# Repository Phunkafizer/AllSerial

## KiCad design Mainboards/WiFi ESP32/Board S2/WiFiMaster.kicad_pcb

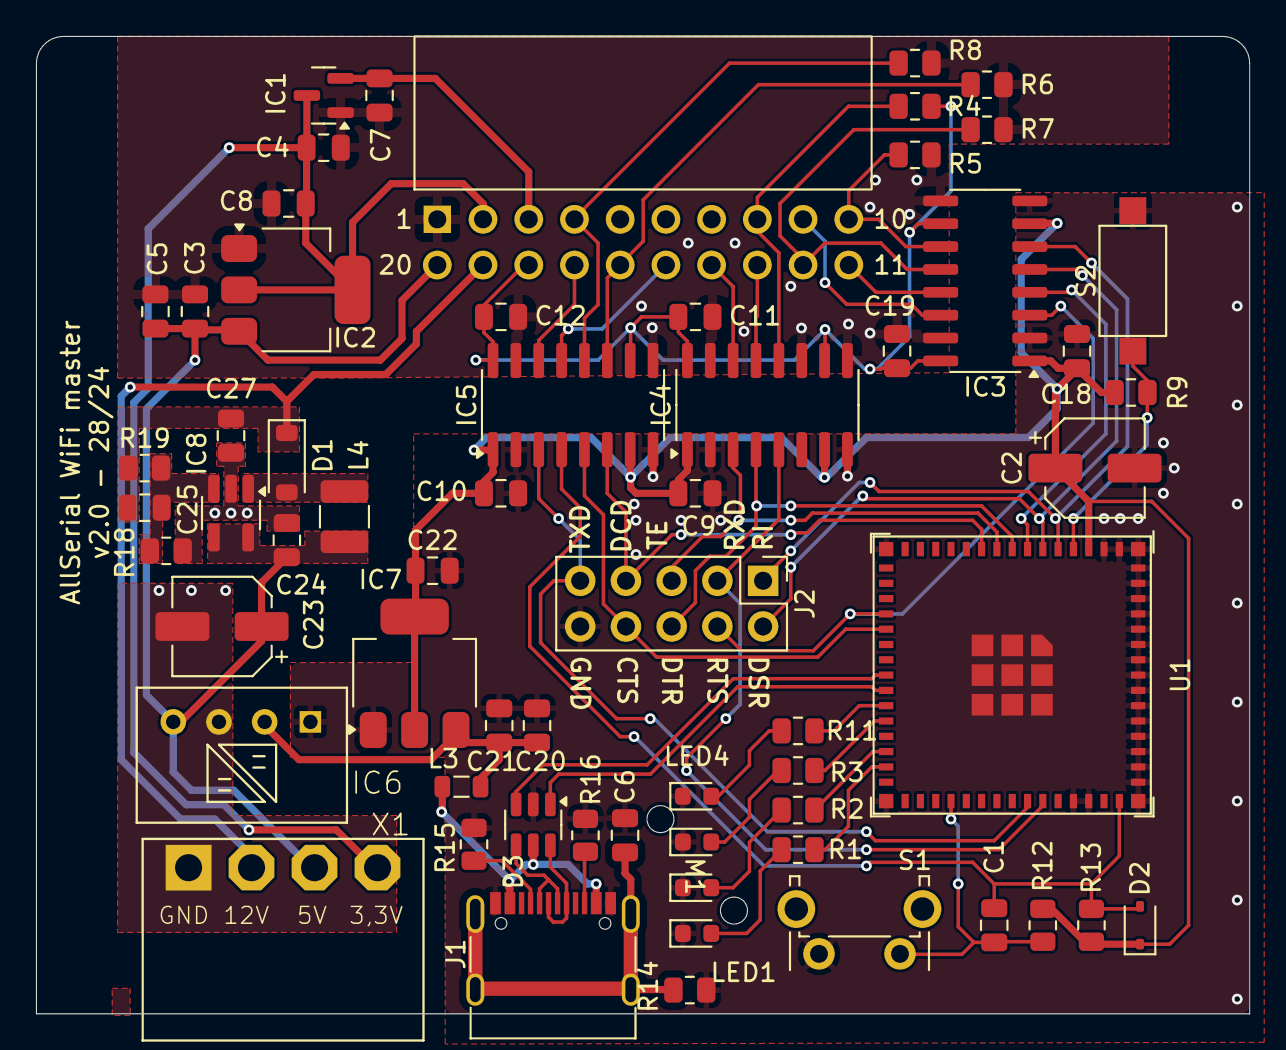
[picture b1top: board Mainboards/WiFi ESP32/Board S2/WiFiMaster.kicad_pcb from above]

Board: 2 copper layers, 67.4 x 54.3 mm, 63 parts (0 on the bottom side), 51 nets.

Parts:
C1, C5, C8, C21, C22, C27: 10µ; C_0805_2012Metric
C2, C23: 100µ; CP_Elec_5x5.9
C3, C9, C10, C11, C12, C18, C19, C20: 100n; C_0805_2012Metric
C4, C7: 1µ; C_0805_2012Metric
C6: 10n; C_0805_2012Metric
C24: 4µ7; C_0805_2012Metric
C25: 22pF; C_0805_2012Metric
D1: MBR0530; D_SOD-123
D2: 1N4148WS; D_SOD-323
D3: USBLC6-2; SOT-23-6
IC1: MCP170X; SOT-23
IC2, IC7: NCP1117ST; SOT-223-3_TabPin2
IC3, IC4, IC5: ADuM142E1BRZ; SOIC-16_3.9x9.9mm_P1.27mm
IC6: IL0505; XPPOWER-ILxxxxS
IC8: TPS61041; SOT-23-5_HandSoldering
J1: USB_C_Receptacle_USB2.0; USB_C_Receptacle_G-Switch_GT-USB-7010ASV
J2: Conn_02x05_Odd_Even; PinHeader_2x05_P2.54mm_Vertical
L3: WE-CBF_0805; L_0805_2012Metric
L4: 10µ; L_1210_3225Metric
LED1: red; LED_0603_1608Metric
LED2: green; LED_0603_1608Metric
LED3: yellow; LED_0603_1608Metric
LED4: blue; LED_0603_1608Metric
M1: Mentor 1296.1004
R1, R2, R3: 120; R_0805_2012Metric
R4, R5, R6, R7, R8: 10k; R_0805_2012Metric
R9, R13, R18: 33k; R_0805_2012Metric
R11: 22; R_0805_2012Metric
R12: 3k3; R_0805_2012Metric
R14: 1M; R_0805_2012Metric
R15, R16: 5k1; R_0805_2012Metric
R19: 300k; R_0805_2012Metric
S1: 31-XX; SW_Tactile_SPST_Angled_PTS645Vx58-2LFS
S2: SW_SPST_CK_RS282G05A3
U1: ESP32-S3-MINI-1; ESP32-S3-MINI-1U
X1: AKL18X-04W; AKL182-04
X2: ALLSERIALMASTERM; MasterBoard

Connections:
+1V8: C7.1, IC1.2 (VO), X2.3 (+1.8V)
+3.3V: C2.1, C9.1, C10.1, C18.1, C22.1, D2.1 (K), IC3.1 (VDDA), IC3.7 (ENA), IC4.1 (VDDA), IC4.7 (ENA), IC5.1 (VDDA), IC5.7 (ENA), IC7.2 (VO), R9.2, R12.2, R13.2, U1.3 (3V3)
+3V3_2: C4.1, C8.1, IC1.3 (VI), IC2.2 (VO), X1.P$4 (S), X2.2 (+3.3V)
+5V: C20.1, C21.1, IC6.2 (+VIN), IC7.3 (VI), L3.2
+5V_2: C3.1, C5.1, C23.1, C24.1, IC2.3 (VI), IC6.4 (+VOUT), IC8.4 (EN), IC8.5 (VIN), L4.1, X1.P$3 (S), X2.20 (+5V)
+12V: C25.1, C27.1, D1.1 (K), R19.1, X1.P$2 (S), X2.19 (+12V)
/BTN: C1.2, R12.1, S1.1, U1.34 (GPIO38)
/CTS_A: IC5.5 (OUTA), J2.8, U1.20 (GPIO16)
/CTS_B: IC5.12 (INB), R8.1, X2.4 (CTS)
/DCD_A: IC5.6 (OUTA), J2.7, U1.10 (GPIO6)
/DCD_B: IC5.11 (INB), R6.1, X2.16 (DCD)
/DSR_A: IC3.5 (OUTA), J2.2, U1.6 (GPIO2)
/DSR_B: IC3.12 (INB), R7.1, X2.12 (DSR)
/DTR_A: IC4.4 (INA), J2.6, U1.8 (GPIO4)
/DTR_B: IC4.13 (OUTB), X2.13 (DTR)
/GP_A: IC3.4 (INA), U1.7 (GPIO3)
/GP_B: IC3.13 (OUTB), X2.11 (GPIO)
/LED1: R1.2, U1.29 (GPIO34)
/LED2: R2.1, U1.28 (GPIO33)
/LED3: R3.1, U1.26 (GPIO26)
/LED4: R11.1, U1.25 (GPIO21)
/RI_A: IC3.6 (OUTA), J2.1, U1.5 (GPIO1)
/RI_B: IC3.11 (INB), R5.1, X2.10 (RI)
/RST: C1.1, D2.2 (A), IC5.4 (INA), R13.1, U1.45 (EN)
/RST_B: IC5.13 (OUTB), X2.15 (RST)
/RTS_A: IC3.3 (INA), J2.4, U1.19 (GPIO15)
/RTS_B: IC3.14 (OUTB), X2.9 (RTS)
/RXD_A: IC4.5 (OUTA), J2.3, U1.40 (GPIO44)
/RXD_B: IC4.12 (INB), R4.2, X2.8 (RXD)
/SHLD: C6.1, J1.S1 (SHIELD), R14.2
/TXD_A: IC5.3 (INA), J2.9, U1.39 (GPIO43)
/TXD_B: IC5.14 (OUTB), X2.17 (TXD)
/TXEN_A: IC4.3 (INA), J2.5, U1.9 (GPIO5)
/TXEN_B: IC4.14 (OUTB), X2.14 (TXEN)
/USB_D+: D3.1 (I/O1), U1.24 (GPIO20)
/USB_D-: D3.3 (I/O2), U1.23 (GPIO19)
GND: C2.2, C6.2, C9.2, C10.2, C18.2, C20.2, C21.2, C22.2, D3.2 (GND), IC3.2 (GNDA), IC3.8 (GNDA), IC4.2 (GNDA), IC4.8 (GNDA), IC5.2 (GNDA), IC5.8 (GNDA), IC6.1 (-VIN), IC7.1 (GND), J1.A1 (GND), J1.A12 (GND), J1.B1 (GND), J1.B12 (GND), J2.10, LED1.1 (K), LED2.1 (K), LED3.1 (K), LED4.1 (K), R14.1, R15.2, R16.2, S1.2, S2.2, U1.1 (GND), U1.2 (GND), U1.42 (GND), U1.43 (GND), U1.46 (GND), U1.47 (GND), U1.48 (GND), U1.49 (GND), U1.50 (GND), U1.51 (GND), U1.52 (GND), U1.53 (GND), U1.54 (GND), U1.55 (GND), U1.56 (GND), U1.57 (GND), U1.58 (GND), U1.59 (GND), U1.60 (GND), U1.61 (GND), U1.62 (GND), U1.63 (GND), U1.64 (GND), U1.65 (GND)
GND2: C3.2, C4.2, C5.2, C7.2, C8.2, C11.2, C12.2, C19.2, C23.2, C24.2, C27.2, IC1.1 (GND), IC2.1 (GND), IC3.9 (GNDB), IC3.15 (GNDB), IC4.9 (GNDB), IC4.11 (INB), IC4.15 (GNDB), IC5.9 (GNDB), IC5.15 (GNDB), IC6.3 (-VOUT), IC8.2 (GND), R5.2, R6.2, R7.2, R8.2, R18.2, X1.P$1 (S), X2.1 (GND)
unnamed: D1.2 (A), IC8.1 (SW), L4.2
unnamed: D3.6 (I/O1), J1.A6 (D+), J1.B6 (D+)
unnamed: D3.4 (I/O2), J1.A7 (D-), J1.B7 (D-)
unnamed: D3.5 (VBUS), J1.A4 (VBUS), J1.A9 (VBUS), J1.B4 (VBUS), J1.B9 (VBUS), L3.1
unnamed: C25.2, IC8.3 (FB), R18.1, R19.2
unnamed: J1.A5 (CC1), R15.1
unnamed: J1.B5 (CC2), R16.1
unnamed: LED1.2 (A), R1.1
unnamed: LED2.2 (A), R2.2
unnamed: LED3.2 (A), R3.2
unnamed: LED4.2 (A), R11.2
unnamed: R9.1, S2.1, U1.4 (GPIO0)
VBUS: C11.1, C12.1, C19.1, IC3.10 (ENB), IC3.16 (VDDB), IC4.10 (ENB), IC4.16 (VDDB), IC5.10 (ENB), IC5.16 (VDDB), R4.1, X2.18 (VIN)

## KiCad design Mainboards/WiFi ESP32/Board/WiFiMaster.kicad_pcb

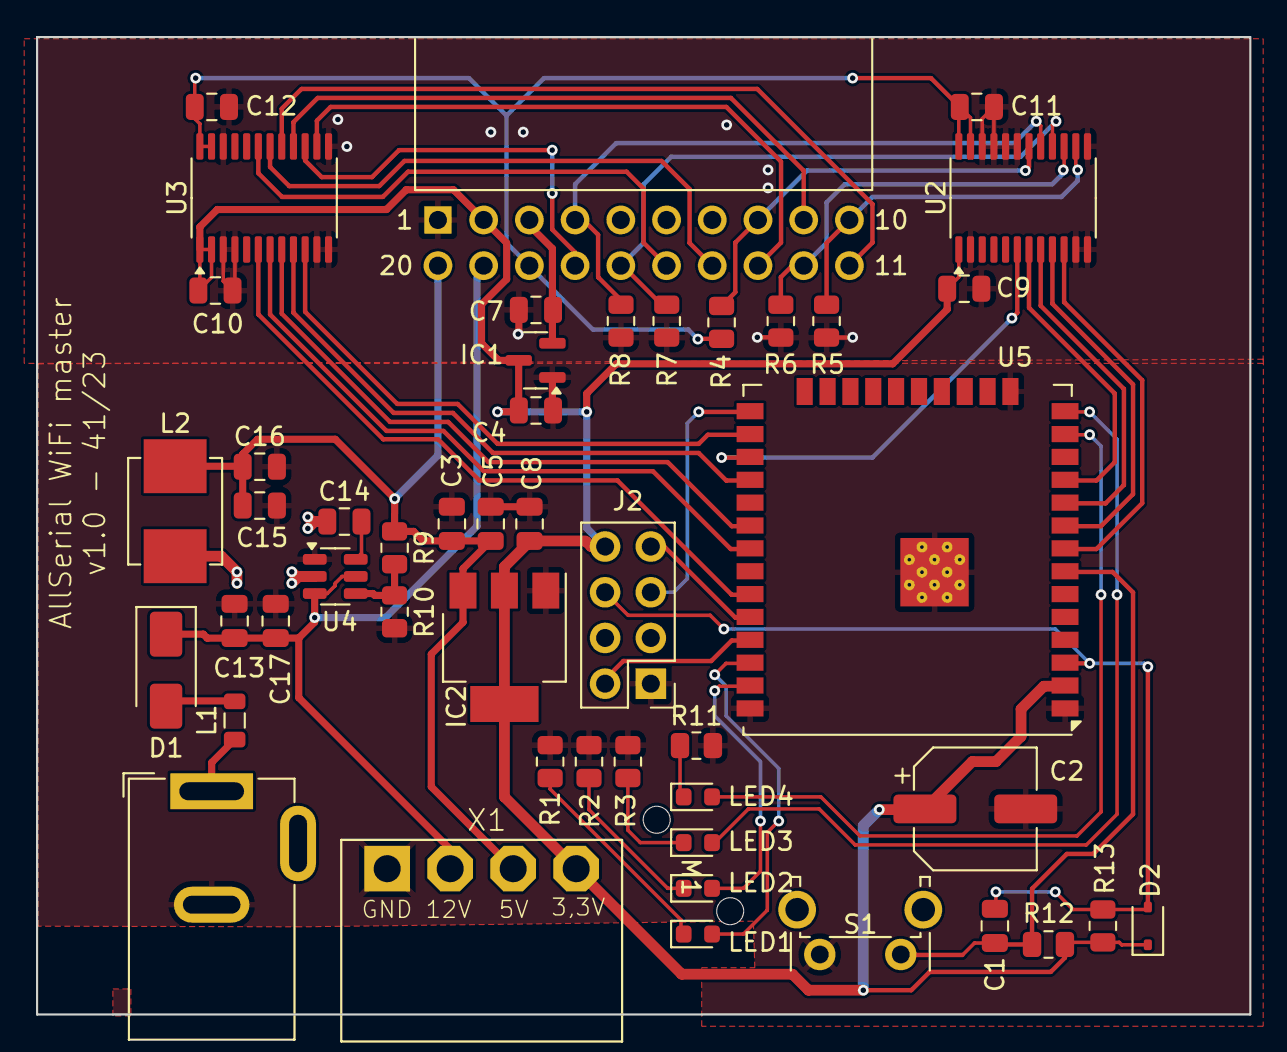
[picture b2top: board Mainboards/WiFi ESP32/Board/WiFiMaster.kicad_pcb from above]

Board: 2 copper layers, 67.4 x 54.3 mm, 49 parts (0 on the bottom side), 45 nets.

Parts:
C1, C5, C8, C13, C17: 10µ; C_0805_2012Metric
C2: 100µ; CP_Elec_6.3x5.4
C3, C9, C10, C11, C12, C14: 100n; C_0805_2012Metric
C4, C7: 1µ; C_0805_2012Metric
C15, C16: 22µ; C_0805_2012Metric
D1: SK 14 DIO; D_SMA
D2: 1N4148WS; D_SOD-323
IC1: MCP170X; SOT-23
IC2: NCP1117ST; SOT-223-3_TabPin2
J1: Barrel_Jack_Switch; BarrelJack_GCT_DCJ200-10-A_Horizontal
J2: Conn_02x04_Odd_Even; PinHeader_2x04_P2.54mm_Vertical
L1: WE-CBF_0805; L_0805_2012Metric
L2: 4µ7; L_Murata_LQH55DN_5.7x5.0mm
LED1: red; LED_0603_1608Metric
LED2: green; LED_0603_1608Metric
LED3: yellow; LED_0603_1608Metric
LED4: blue; LED_0603_1608Metric
M1: Mentor 1296.1004
R1, R2, R3: 120; R_0805_2012Metric
R4, R5, R6, R7, R8, R10: 10k; R_0805_2012Metric
R9: 54k9; R_0805_2012Metric
R11: 22; R_0805_2012Metric
R12: 3k3; R_0805_2012Metric
R13: 33k; R_0805_2012Metric
S1: 31-XX; SW_Tactile_SPST_Angled_PTS645Vx58-2LFS
U2, U3: SN74LVC8T245; TSSOP-24_4.4x7.8mm_P0.65mm
U4: TPS56220; SOT-23-6
U5: ESP32-WROOM-32U
X1: AKL18X-04W; AKL182-04
X2: ALLSERIALMASTERM; MasterBoard

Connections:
+1V8: C7.1, IC1.2 (VO), X2.3 (+1.8V)
+3.3V: C2.1, C4.1, C8.1, C9.1, C10.1, D2.1 (K), IC1.3 (VI), IC2.2 (VO), J2.8, R12.2, R13.2, U2.1 (Vcca), U3.1 (Vcca), U3.2 (DIR), U5.2 (VDD), X1.P$4 (S), X2.2 (+3.3V)
+5V: C3.1, C5.1, C15.1, C16.1, IC2.3 (VI), L2.2, R9.1, X1.P$3 (S), X2.20 (+5V)
+12V: C13.1, C17.1, D1.1 (K), U4.3 (VIN), U4.5 (EN), X1.P$2 (S), X2.19 (+12V)
/BTN: C1.2, R12.1, S1.1, U5.7 (IO35)
/CTS_A: U2.7 (A5), U5.11 (IO26)
/CTS_B: R8.1, U2.17 (B5), X2.4 (CTS)
/DCD_A: U2.8 (A6), U5.10 (IO25)
/DCD_B: R7.1, U2.16 (B6), X2.16 (DCD)
/DSR_A: U2.9 (A7), U5.9 (IO33)
/DSR_B: R6.1, U2.15 (B7), X2.12 (DSR)
/DTR_A: U3.10 (A8), U5.26 (IO4)
/DTR_B: U3.14 (B8), X2.13 (DTR)
/GP_A: U3.7 (A5), U5.31 (IO19)
/GP_B: U3.17 (B5), X2.11 (GPIO)
/IO0: J2.5, U5.25 (IO0)
/LED1: LED1.2 (A), U5.36 (IO22)
/LED2: LED2.2 (A), U5.37 (IO23)
/LED3: LED3.2 (A), U5.14 (IO12)
/LED4: LED4.2 (A), U5.13 (IO14)
/RI_A: U2.10 (A8), U5.8 (IO32)
/RI_B: R5.1, U2.14 (B8), X2.10 (RI)
/RST: C1.1, D2.2 (A), J2.6, R13.1, U5.3 (EN)
/RST_B: U3.19 (B3), X2.15 (RST)
/RTS_A: U3.8 (A6), U5.30 (IO18)
/RTS_B: U3.16 (B6), X2.9 (RTS)
/RXD: J2.7, U5.34 (RXD0/IO3)
/RXD_A: U2.6 (A4), U5.27 (IO16)
/RXD_B: R4.2, U2.18 (B4), X2.8 (RXD)
/TXD: J2.2, U5.35 (TXD0/IO1)
/TXD_A: U3.9 (A7), U5.28 (IO17)
/TXD_B: U3.15 (B7), X2.17 (TXD)
/TXEN_A: U3.6 (A4), U5.33 (IO21)
/TXEN_B: U3.18 (B4), X2.14 (TXEN)
GND: C2.2, C3.2, C4.2, C5.2, C7.2, C8.2, C9.2, C10.2, C11.2, C12.2, C13.2, C15.2, C16.2, C17.2, IC1.1 (GND), IC2.1 (GND), J1.2, J2.1, R1.1, R2.2, R3.2, R5.2, R6.2, R7.2, R8.2, R10.2, R11.2, S1.2, U2.2 (DIR), U2.11 (GND), U2.12 (GND), U2.13 (GND), U2.19 (B3), U2.20 (B2), U2.21 (B1), U2.22 (OE), U3.3 (A1), U3.4 (A2), U3.11 (GND), U3.12 (GND), U3.13 (GND), U3.22 (OE), U4.1 (GND), U5.1 (GND), U5.15 (GND), U5.38 (GND), U5.39 (GND), X1.P$1 (S), X2.1 (GND)
unnamed: D1.2 (A), L1.2
unnamed: J1.1, L1.1
unnamed: LED1.1 (K), R1.2
unnamed: LED2.1 (K), R2.1
unnamed: LED3.1 (K), R3.1
unnamed: LED4.1 (K), R11.1
unnamed: C14.2, U4.6 (BOOT)
unnamed: R9.2, R10.1, U4.4 (FB)
unnamed: C14.1, L2.1, U4.2 (SW)
VBUS: C11.1, C12.1, R4.1, U2.23 (Vccb), U2.24 (Vccb), U3.23 (Vccb), U3.24 (Vccb), X2.18 (VIN)

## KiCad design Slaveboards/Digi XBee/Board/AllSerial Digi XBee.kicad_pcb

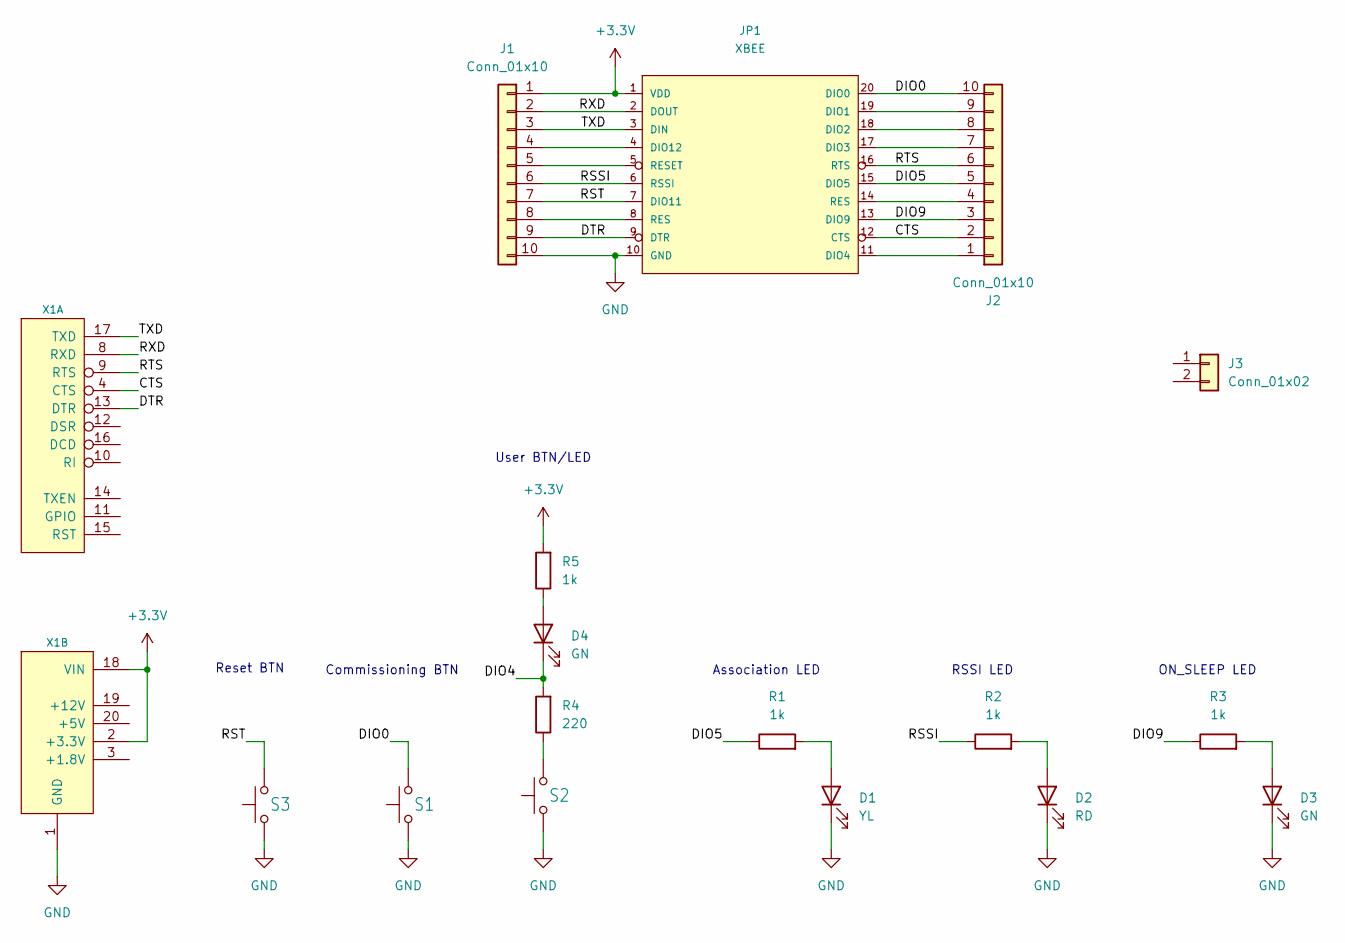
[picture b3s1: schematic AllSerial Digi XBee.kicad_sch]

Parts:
D1: YL; LED_0805_2012Metric
D2: RD; LED_0805_2012Metric
D3, D4: GN; LED_0805_2012Metric
J1, J2: Conn_01x10; PinHeader_1x10_P2.54mm_Vertical
J3: Conn_01x02; Metz_PT11302HBBN_182
JP1: XBEE
R1, R2, R3, R5: 1k; R_0805_2012Metric
R4: 220; R_0805_2012Metric
S1, S2, S3: 31-XX; SW_SPST_CK_RS282G05A3; LCSC C2837543
X1: AllSerial Slaveboard; SlaveBoard

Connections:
+3.3V: J1.1, JP1.1 (VDD), R5.2, X1.2 (+3.3V), X1.18 (VIN)
/CTS: J2.2, JP1.12 (CTS), X1.4 (CTS)
/DIO0: J2.10, JP1.20 (DIO0), S1.1
/DIO4: D4.1 (K), R4.2
/DIO5: J2.5, JP1.15 (DIO5), R1.1
/DIO9: J2.3, JP1.13 (DIO9), R3.1
/DTR: J1.9, JP1.9 (DTR), X1.13 (DTR)
/RSSI: J1.6, JP1.6 (RSSI), R2.1
/RST: J1.7, JP1.7 (DIO11), S3.1
/RTS: J2.6, JP1.16 (RTS), X1.9 (RTS)
/RXD: J1.2, JP1.2 (DOUT), X1.8 (RXD)
/TXD: J1.3, JP1.3 (DIN), X1.17 (TXD)
GND: D1.1 (K), D2.1 (K), D3.1 (K), J1.10, JP1.10 (GND), S1.2, S2.2, S3.2, X1.1 (GND)
unnamed: D1.2 (A), R1.2
unnamed: D2.2 (A), R2.2
unnamed: D3.2 (A), R3.2
unnamed: D4.2 (A), R5.1
unnamed: J1.4, JP1.4 (DIO12)
unnamed: J1.5, JP1.5 (RESET)
unnamed: J1.8, JP1.8 (RES)
unnamed: J2.1, JP1.11 (DIO4)
unnamed: J2.4, JP1.14 (RES)
unnamed: J2.7, JP1.17 (DIO3)
unnamed: J2.8, JP1.18 (DIO2)
unnamed: J2.9, JP1.19 (DIO1)
unnamed: R4.1, S2.1

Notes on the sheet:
User BTN/LED
RSSI LED
Commissioning BTN
Reset BTN
ON_SLEEP LED
Association LED

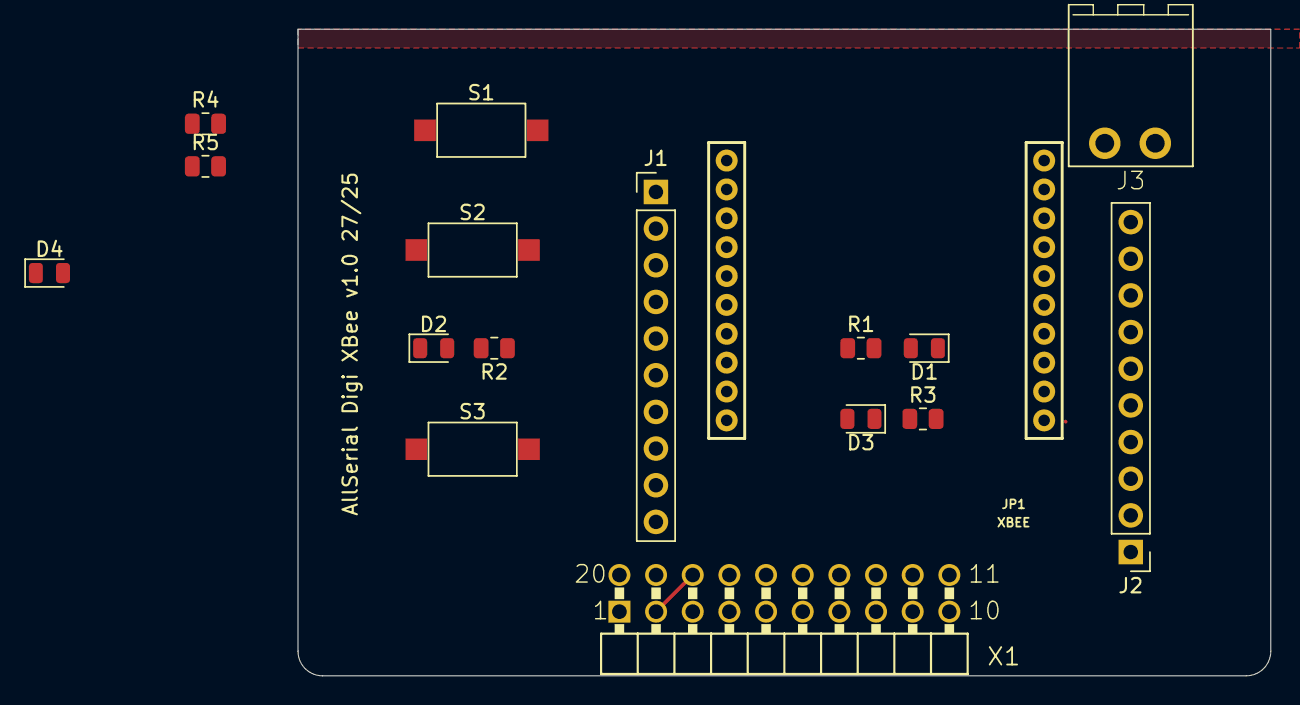
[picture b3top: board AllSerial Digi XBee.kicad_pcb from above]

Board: 2 copper layers, 67.4 x 44.8 mm, 17 parts (0 on the bottom side), 26 nets.
